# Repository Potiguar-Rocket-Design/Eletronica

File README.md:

# Potiguar-Rocket-Design-Eletronica

Acervo de códigos e conteúdos para documentação.

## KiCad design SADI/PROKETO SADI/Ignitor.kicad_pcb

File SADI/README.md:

# Sistema de Aquisição de Dados e Ignição - SADI

## INTRODUÇÃO

Os testes estáticos de motores necessitavam de um dispositivo capaz de ignitar o propelente disposto na câmara de combustão. Tal dispositivo desenvolvido pela equipe inicialmente atendia a questão, mas com o tempo o dispositivo começou a apresentar falhas que geravam enumeras tentativas e até abortameto dos teste, com isso foi pensado em uma versão 2 capaz de não só ignitar o propelente, mas fazer aquisição de dados da célula de carga gerada pelo empuxo do motor. 
A seguir será feito apresentado como foi arquitetado o aparelho e um manual de uso para todos os membros da equipe.

## CONSTRUÇÃO

O softawe utilizado para o desenvolvimento do projeto foi o Kicad -  http://kicad-pcb.org/, o esquemático onde foram feitas as ligações entre os componentes e o projeto da placa de circuito impresso (PCI). A figura 1 mostra-se a visão geral do projeto dividindo

### Figura 1 -  Esquemático SADI

## CONCLUSÃO

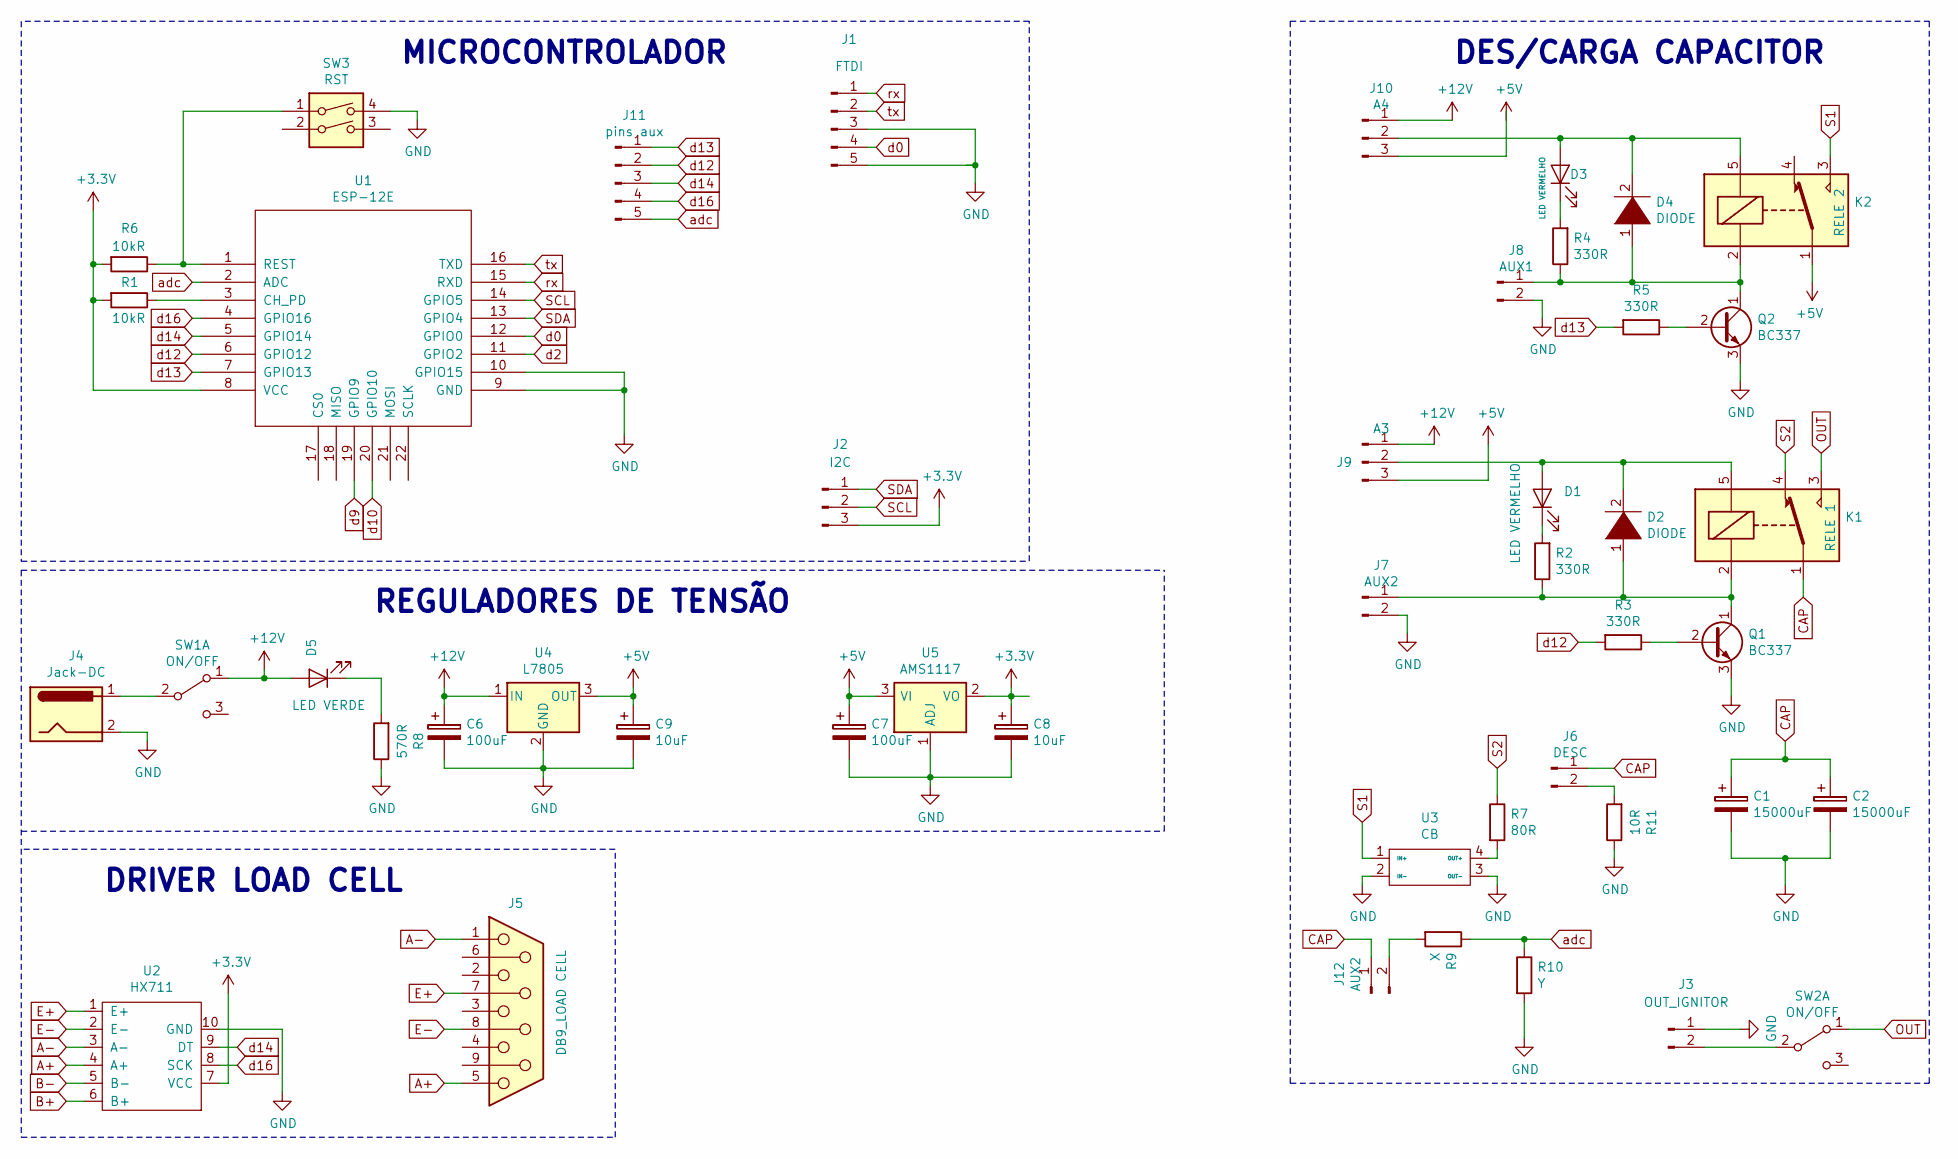
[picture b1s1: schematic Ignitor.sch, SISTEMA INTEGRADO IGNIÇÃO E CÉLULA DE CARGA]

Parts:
C1, C2: 15000uF; CP_Radial_D22.0mm_P10.00mm_SnapIn
C6, C7: 100uF; CP_Radial_D4.0mm_P2.00mm
C8, C9: 10uF; CP_Radial_D4.0mm_P2.00mm
D1, D3: LED VERMELHO; LED_D3.0mm
D2, D4: DIODE; D_DO-41_SOD81_P12.70mm_Horizontal
D5: LED VERDE; LED_D3.0mm
J1: FTDI; PinHeader_1x05_P2.54mm_Vertical
J2: I2C; PinHeader_1x03_P2.54mm_Vertical
J3: OUT_IGNITOR; TerminalBlock_Altech_AK300-2_P5.00mm
J4: Jack-DC; Jack_Horizontal
J5: DB9_LOAD CELL; DSUB-9_Female_Horizontal_P2.77x2.84mm_EdgePinOffset9.90mm_H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
J6: DESC; PinSocket_1x02_P2.54mm_Vertical
J7, J12: AUX2; PinSocket_1x02_P2.54mm_Vertical
J8: AUX1; PinSocket_1x02_P2.54mm_Vertical
J9: A3; PinHeader_1x03_P2.54mm_Vertical
J10: A4; PinHeader_1x03_P2.54mm_Vertical
J11: pins aux; PinHeader_1x05_P2.54mm_Vertical
K1: RELE 1; Relay_SPDT_Omron-G5LE-1
K2: RELE 2; Relay_SPDT_Omron-G5LE-1
Q1, Q2: BC337; TO-92_Inline
R1, R6: 10kR; R_Axial_DIN0207_L6.3mm_D2.5mm_P15.24mm_Horizontal
R2, R3, R4, R5: 330R; R_Axial_DIN0207_L6.3mm_D2.5mm_P15.24mm_Horizontal
R7: 80R; R_Axial_DIN0207_L6.3mm_D2.5mm_P15.24mm_Horizontal
R8: 570R; R_Axial_DIN0207_L6.3mm_D2.5mm_P15.24mm_Horizontal
R9: X; R_Axial_DIN0207_L6.3mm_D2.5mm_P15.24mm_Horizontal
R10: Y; R_Axial_DIN0207_L6.3mm_D2.5mm_P15.24mm_Horizontal
R11: 10R; R_Axial_DIN0207_L6.3mm_D2.5mm_P15.24mm_Horizontal
SW1, SW2: ON/OFF; switch_mmp122-r
SW3: RST; SW_TH_Tactile_Omron_B3F-10xx
U1: ESP-12E; ESP12E
U2: HX711
U3: CB
U4: L7805; TO-220-3_Vertical
U5: AMS1117; SOT-223-3_TabPin2

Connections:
+3V3: C8.1, J2.3, R1.2, R6.2, U1.8 (VCC), U2.7 (VCC), U5.2 (VO)
+12V: C6.1, D5.2 (A), J9.1, J10.1, SW1.1 (A), U4.1 (IN)
A+: J5.5, U2.4 (A+)
A-: J5.1, U2.3 (A-)
B+: U2.6 (B+)
B-: U2.5 (B-)
CAP: C1.1, C2.1, J6.1, J12.1, K1.1
E+: J5.7, U2.1 (E+)
E-: J5.8, U2.2 (E-)
GND: C1.2, C2.2, C6.2, C7.2, C8.2, C9.2, J1.3, J1.5, J3.1, J4.2, J7.2, J8.2, Q1.3 (E), Q2.3 (E), R8.1, R10.2, R11.1, SW3.4, U1.9 (GND), U1.10 (GPIO15), U2.10 (GND), U3.2 (IN-), U3.3 (OUT-), U4.2 (GND), U5.1 (ADJ)
unnamed: D1.1 (K), R2.2
unnamed: D1.2 (A), D2.2 (A), J9.2, K1.5
unnamed: D2.1 (K), J7.1, K1.2, Q1.1 (C), R2.1
unnamed: D3.1 (K), R4.2
unnamed: D3.2 (A), D4.2 (A), J10.2, K2.5
unnamed: D4.1 (K), J8.1, K2.2, Q2.1 (C), R4.1
unnamed: D5.1 (K), R8.2
unnamed: J3.2, SW2.2 (B)
unnamed: J4.1, SW1.2 (B)
unnamed: J6.2, R11.2
unnamed: J12.2, R9.2
unnamed: Q1.2 (B), R3.1
unnamed: Q2.2 (B), R5.1
unnamed: R1.1, U1.3 (CH_PD)
unnamed: R6.1, SW3.1, U1.1 (REST)
unnamed: R7.2, U3.4 (OUT+)
OUT: K1.3, SW2.1 (A)
S1: K2.3, U3.1 (IN+)
S2: K1.4, R7.1
SCL: J2.2, U1.14 (GPIO5)
SDA: J2.1, U1.13 (GPIO4)
adc: J11.5, R9.1, R10.1, U1.2 (ADC)
d0: J1.4, U1.12 (GPIO0)
d2: U1.11 (GPIO2)
d9: U1.19 (GPIO9)
d10: U1.20 (GPIO10)
d12: J11.2, R3.2, U1.6 (GPIO12)
d13: J11.1, R5.2, U1.7 (GPIO13)
d14: J11.3, U1.5 (GPIO14), U2.9 (DT)
d16: J11.4, U1.4 (GPIO16), U2.8 (SCK)
rx: J1.1, U1.15 (RXD)
tx: J1.2, U1.16 (TXD)

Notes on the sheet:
MICROCONTROLADOR
DRIVER LOAD CELL
REGULADORES DE TENSÃO
DES/CARGA CAPACITOR

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
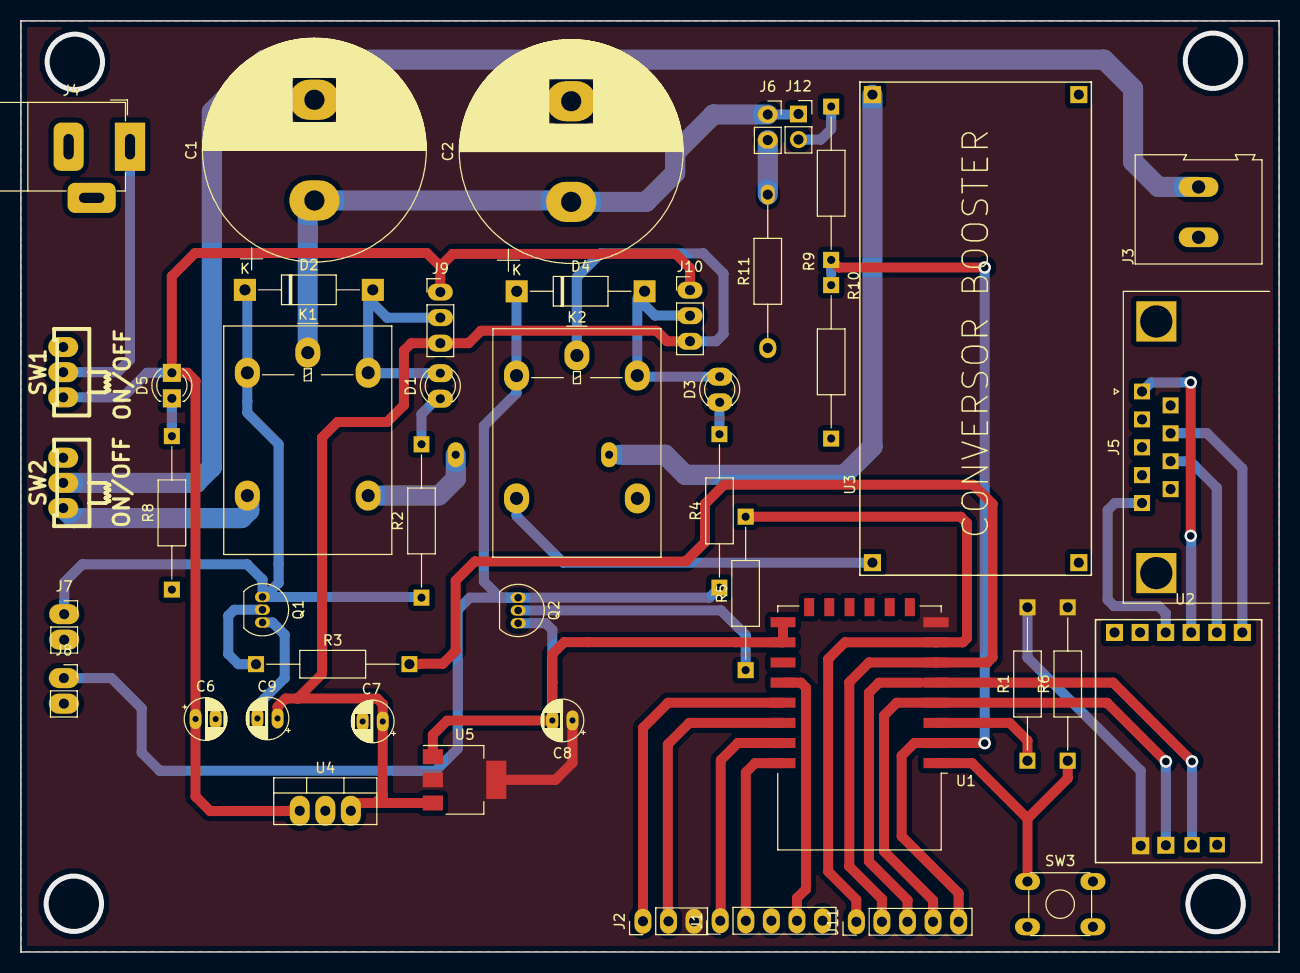
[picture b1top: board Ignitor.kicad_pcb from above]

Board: 2 copper layers, 125.0 x 92.5 mm, 46 parts (1 on the bottom side), 38 nets.

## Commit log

2019-03-26 Rename mmq.sce to Regressão Linear.sce
2019-03-27 Rename ReadMe.md to LeiaMe.md
2019-03-28 Imagem da calibração da célula de carga.
2019-03-28 Create Nada a comenta
2019-03-29 Rename readme to README.md
2019-10-08 arquivos
2019-10-08 adicionando pasta
2019-10-08 adicionando pastas
2019-10-13 13-10-2019
